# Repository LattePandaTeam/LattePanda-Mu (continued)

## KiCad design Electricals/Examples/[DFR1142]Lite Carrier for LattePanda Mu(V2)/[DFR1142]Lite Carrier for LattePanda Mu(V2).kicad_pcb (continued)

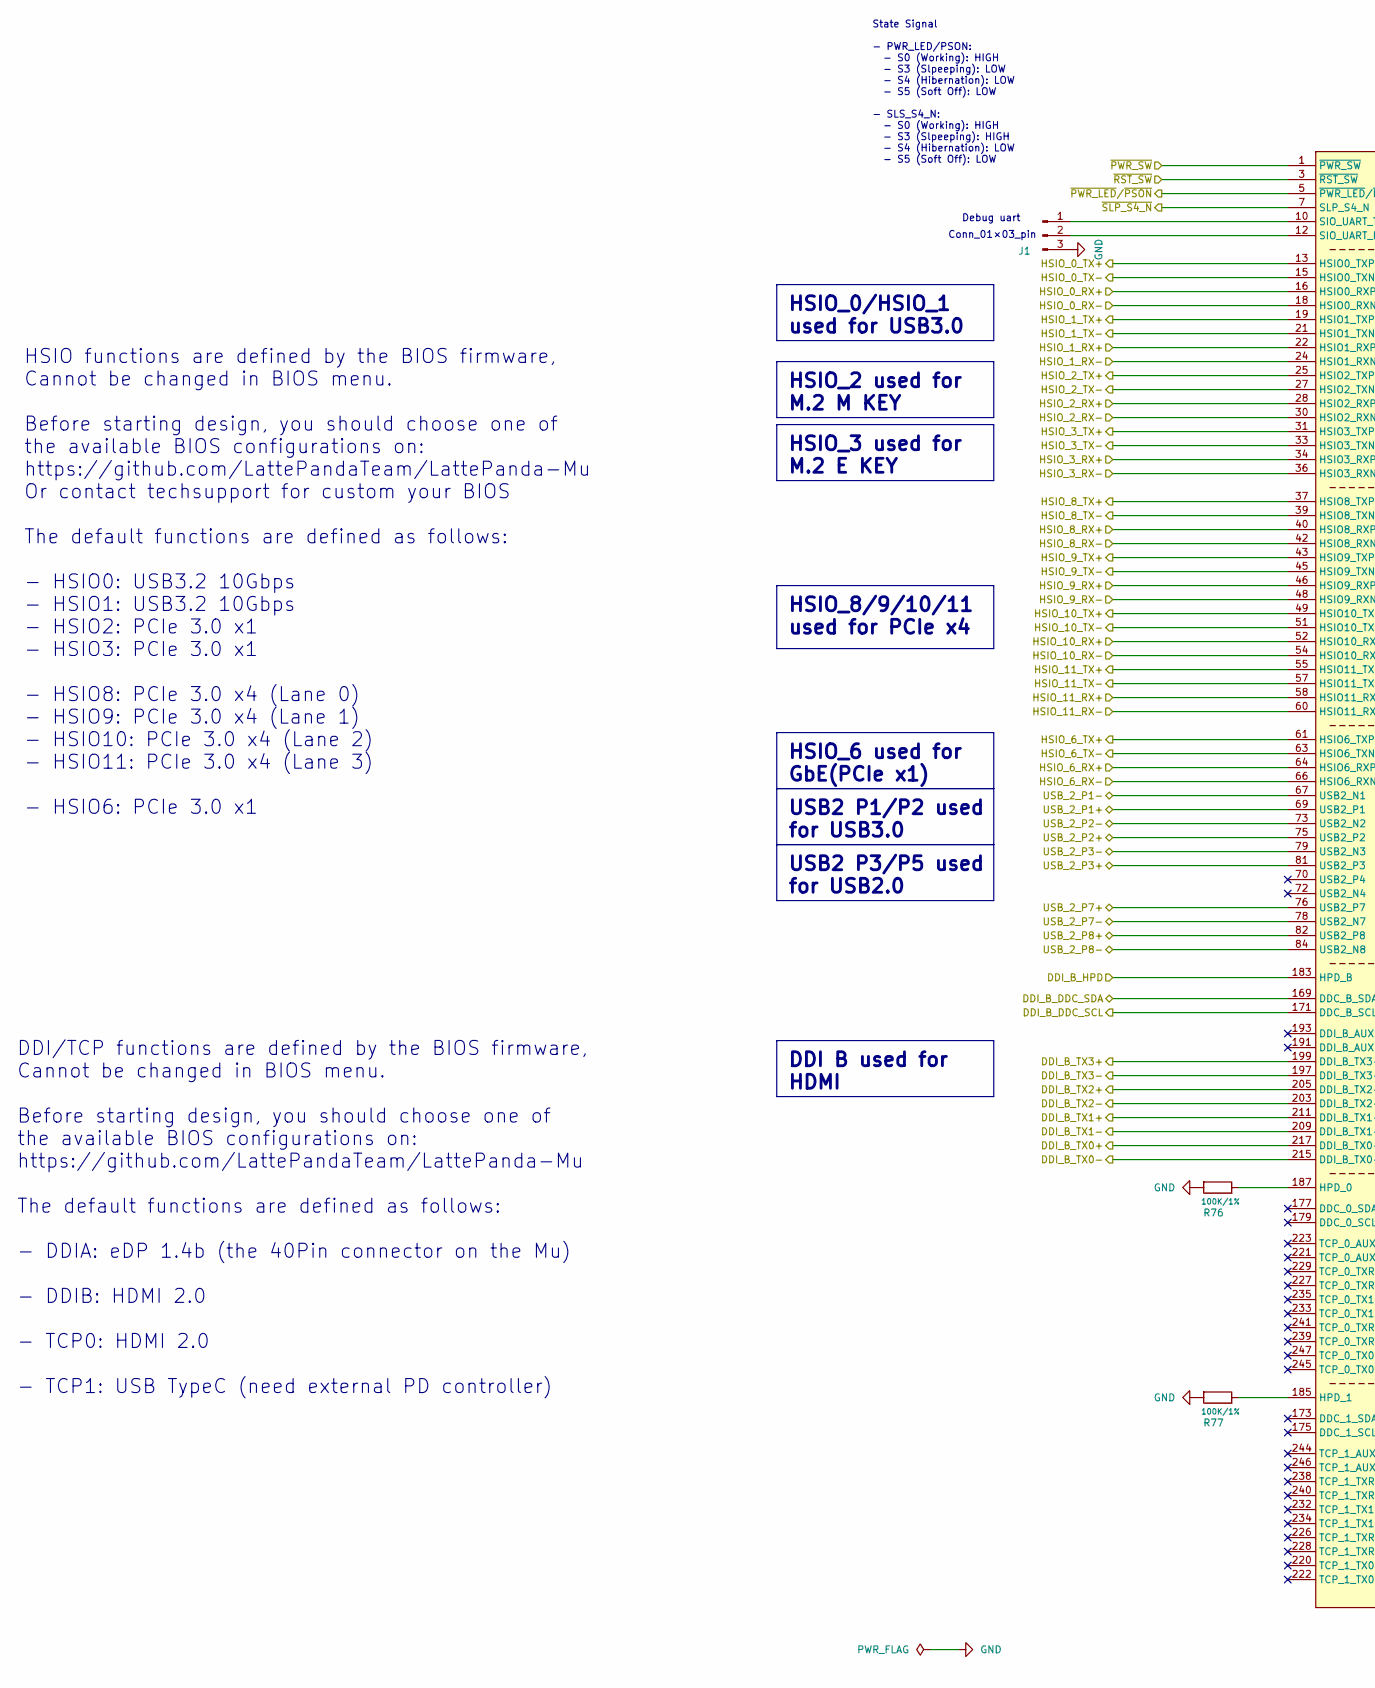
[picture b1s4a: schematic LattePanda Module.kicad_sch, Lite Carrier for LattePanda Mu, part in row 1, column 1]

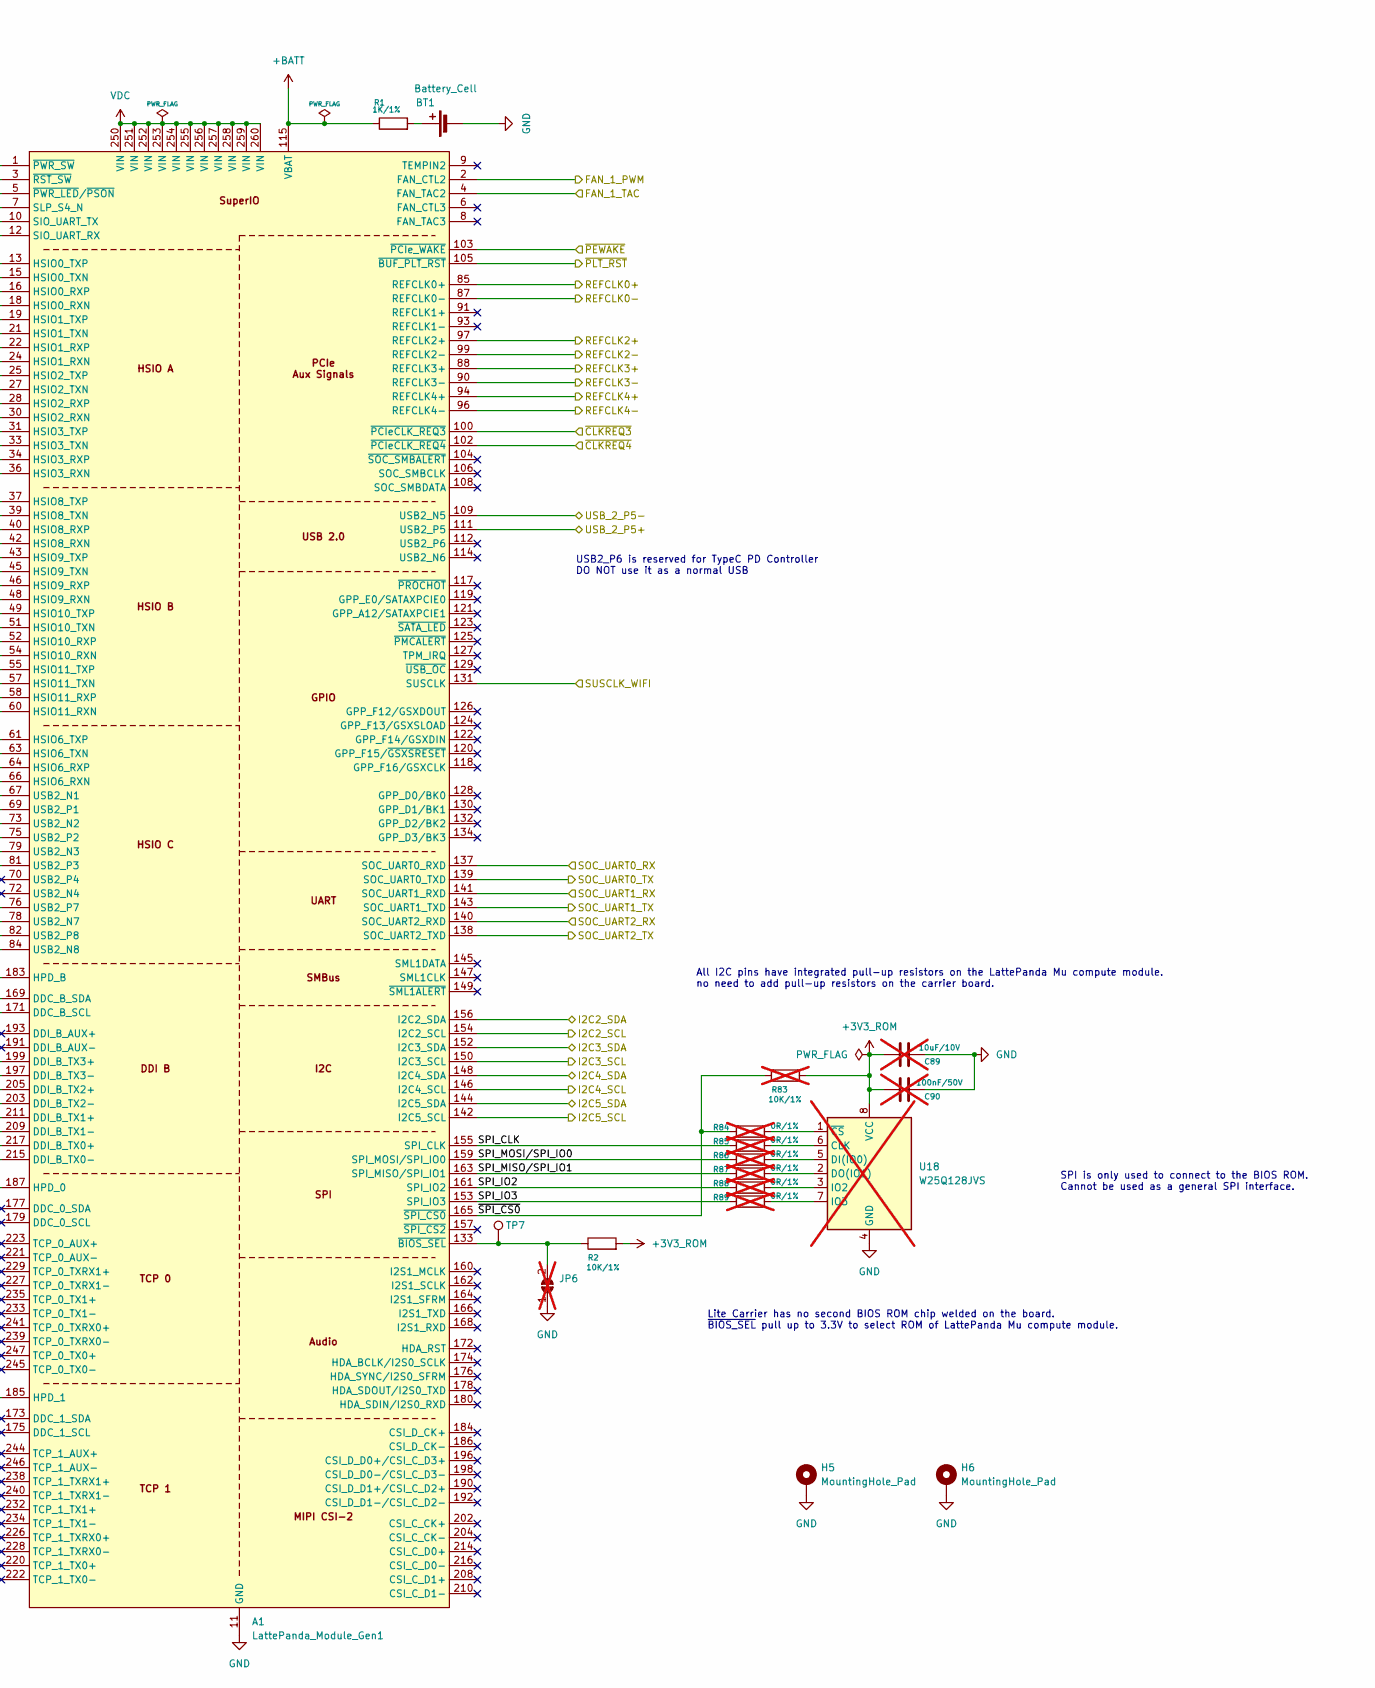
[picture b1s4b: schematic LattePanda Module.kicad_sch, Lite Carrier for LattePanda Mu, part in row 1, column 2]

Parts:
A1: LattePanda_Module_Gen1; DDR4_SODIMM_260P_8.0H_STD
BT1: Battery_Cell; Battery_Holder_CR1220_S8411-45R
C89: 10uF/10V; C_0402; not fitted
C90: 100nF/50V; C_0402; not fitted
H5, H6: MountingHole_Pad; MountingHole_3mm_M2_Pad_TopOnly
J1: Conn_01x03_Pin; PinHeader_1x03_P2.54mm_Vertical
JP6: SolderJumper_2_Open; SolderJumper-2_P1.3mm_Open_TrianglePad1.0x1.5mm; not fitted
R1: 1K/1%; R_0402
R2: 10K/1%; R_0402
R76, R77: 100K/1%; R_0402
R83: 10K/1%; R_0402; not fitted
R84, R85, R86, R87, R88, R89: 0R/1%; R_0402; not fitted
TP7: TestPoint; TestPoint_Pad_D1.5mm
U18: W25Q128JVS; SOIC-8_5.23x5.23mm_P1.27mm; not fitted

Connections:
+3V3_ROM: C89.2, C90.2, R2.2, R83.2, U18.8 (VCC); also elsewhere on the board
+BATT: A1.115 (VBAT), R1.1
/Fan_Temp/FAN_1_PWM: A1.2 (FAN_CTL2); also elsewhere on the board
/Fan_Temp/FAN_1_TAC: A1.4 (FAN_TAC2); also elsewhere on the board
/GPIO/I2C2_SCL: A1.154 (I2C2_SCL); also elsewhere on the board
/GPIO/I2C2_SDA: A1.156 (I2C2_SDA); also elsewhere on the board
/GPIO/I2C3_SCL: A1.150 (I2C3_SCL); also elsewhere on the board
/GPIO/I2C3_SDA: A1.152 (I2C3_SDA); also elsewhere on the board
/GPIO/I2C4_SCL: A1.146 (I2C4_SCL); also elsewhere on the board
/GPIO/I2C4_SDA: A1.148 (I2C4_SDA); also elsewhere on the board
/GPIO/I2C5_SCL: A1.142 (I2C5_SCL); also elsewhere on the board
/GPIO/I2C5_SDA: A1.144 (I2C5_SDA); also elsewhere on the board
/GPIO/SOC_UART0_RX: A1.137 (SOC_UART0_RXD); also elsewhere on the board
/GPIO/SOC_UART0_TX: A1.139 (SOC_UART0_TXD); also elsewhere on the board
/GPIO/SOC_UART1_RX: A1.141 (SOC_UART1_RXD); also elsewhere on the board
/GPIO/SOC_UART1_TX: A1.143 (SOC_UART1_TXD); also elsewhere on the board
/GPIO/SOC_UART2_RX: A1.140 (SOC_UART2_RXD); also elsewhere on the board
/GPIO/SOC_UART2_TX: A1.138 (SOC_UART2_TXD); also elsewhere on the board
/Gigabit Ethernet/GbE_PCIe_CLK+: A1.94 (REFCLK4+); also elsewhere on the board
/Gigabit Ethernet/GbE_PCIe_CLK-: A1.96 (REFCLK4-); also elsewhere on the board
/Gigabit Ethernet/GbE_PCIe_RX+: A1.64 (HSIO6_RXP); also elsewhere on the board
/Gigabit Ethernet/GbE_PCIe_RX-: A1.66 (HSIO6_RXN); also elsewhere on the board
/Gigabit Ethernet/GbE_PCIe_TX+: A1.61 (HSIO6_TXP); also elsewhere on the board
/Gigabit Ethernet/GbE_PCIe_TX-: A1.63 (HSIO6_TXN); also elsewhere on the board
/Gigabit Ethernet/~CLKREQ4: A1.102 (~PCIeCLK_REQ4); also elsewhere on the board
/HDMI/DDI_B_DDC_SCL: A1.171 (DDC_B_SCL); also elsewhere on the board
/HDMI/DDI_B_DDC_SDA: A1.169 (DDC_B_SDA); also elsewhere on the board
/HDMI/DDI_B_HPD: A1.183 (HPD_B); also elsewhere on the board
/HDMI/DDI_B_TX0+: A1.217 (DDI_B_TX0+); also elsewhere on the board
/HDMI/DDI_B_TX0-: A1.215 (DDI_B_TX0-); also elsewhere on the board
/HDMI/DDI_B_TX1+: A1.211 (DDI_B_TX1+); also elsewhere on the board
/HDMI/DDI_B_TX1-: A1.209 (DDI_B_TX1-); also elsewhere on the board
/HDMI/DDI_B_TX2+: A1.205 (DDI_B_TX2+); also elsewhere on the board
/HDMI/DDI_B_TX2-: A1.203 (DDI_B_TX2-); also elsewhere on the board
/HDMI/DDI_B_TX3+: A1.199 (DDI_B_TX3+); also elsewhere on the board
/HDMI/DDI_B_TX3-: A1.197 (DDI_B_TX3-); also elsewhere on the board
/LattePanda Module/HSIO_0_TX+: A1.13 (HSIO0_TXP); also elsewhere on the board
/LattePanda Module/HSIO_0_TX-: A1.15 (HSIO0_TXN); also elsewhere on the board
/LattePanda Module/HSIO_1_TX+: A1.19 (HSIO1_TXP); also elsewhere on the board
/LattePanda Module/HSIO_1_TX-: A1.21 (HSIO1_TXN); also elsewhere on the board
/LattePanda Module/HSIO_2_RX+: A1.28 (HSIO2_RXP); also elsewhere on the board
/LattePanda Module/HSIO_2_RX-: A1.30 (HSIO2_RXN); also elsewhere on the board
/LattePanda Module/HSIO_2_TX+: A1.25 (HSIO2_TXP); also elsewhere on the board
/LattePanda Module/HSIO_2_TX-: A1.27 (HSIO2_TXN); also elsewhere on the board
/LattePanda Module/HSIO_3_RX+: A1.34 (HSIO3_RXP); also elsewhere on the board
/LattePanda Module/HSIO_3_RX-: A1.36 (HSIO3_RXN); also elsewhere on the board
/LattePanda Module/HSIO_3_TX+: A1.31 (HSIO3_TXP); also elsewhere on the board
/LattePanda Module/HSIO_3_TX-: A1.33 (HSIO3_TXN); also elsewhere on the board
/LattePanda Module/HSIO_8_RX+: A1.40 (HSIO8_RXP); also elsewhere on the board
/LattePanda Module/HSIO_8_RX-: A1.42 (HSIO8_RXN); also elsewhere on the board
/LattePanda Module/HSIO_8_TX+: A1.37 (HSIO8_TXP); also elsewhere on the board
/LattePanda Module/HSIO_8_TX-: A1.39 (HSIO8_TXN); also elsewhere on the board
/LattePanda Module/HSIO_9_RX+: A1.46 (HSIO9_RXP); also elsewhere on the board
/LattePanda Module/HSIO_9_RX-: A1.48 (HSIO9_RXN); also elsewhere on the board
/LattePanda Module/HSIO_9_TX+: A1.43 (HSIO9_TXP); also elsewhere on the board
/LattePanda Module/HSIO_9_TX-: A1.45 (HSIO9_TXN); also elsewhere on the board
/LattePanda Module/HSIO_10_RX+: A1.52 (HSIO10_RXP); also elsewhere on the board
/LattePanda Module/HSIO_10_RX-: A1.54 (HSIO10_RXN); also elsewhere on the board
/LattePanda Module/HSIO_10_TX+: A1.49 (HSIO10_TXP); also elsewhere on the board
/LattePanda Module/HSIO_10_TX-: A1.51 (HSIO10_TXN); also elsewhere on the board
/LattePanda Module/HSIO_11_RX+: A1.58 (HSIO11_RXP); also elsewhere on the board
/LattePanda Module/HSIO_11_RX-: A1.60 (HSIO11_RXN); also elsewhere on the board
/LattePanda Module/HSIO_11_TX+: A1.55 (HSIO11_TXP); also elsewhere on the board
/LattePanda Module/HSIO_11_TX-: A1.57 (HSIO11_TXN); also elsewhere on the board
/LattePanda Module/REFCLK0+: A1.85 (REFCLK0+); also elsewhere on the board
/LattePanda Module/REFCLK0-: A1.87 (REFCLK0-); also elsewhere on the board
/LattePanda Module/REFCLK2+: A1.97 (REFCLK2+); also elsewhere on the board
/LattePanda Module/REFCLK2-: A1.99 (REFCLK2-); also elsewhere on the board
/LattePanda Module/REFCLK3+: A1.88 (REFCLK3+); also elsewhere on the board
/LattePanda Module/REFCLK3-: A1.90 (REFCLK3-); also elsewhere on the board
/LattePanda Module/SPI_CLK: A1.155 (SPI_CLK), R85.2
/LattePanda Module/SPI_IO2: A1.161 (SPI_IO2), R88.2
/LattePanda Module/SPI_IO3: A1.153 (SPI_IO3), R89.2
/LattePanda Module/SPI_MISO/SPI_IO1: A1.163 (SPI_MISO/SPI_IO1), R87.2
/LattePanda Module/SPI_MOSI/SPI_IO0: A1.159 (SPI_MOSI/SPI_IO0), R86.2
/LattePanda Module/SUSCLK_WIFI: A1.131 (SUSCLK); also elsewhere on the board
/LattePanda Module/USB_2_P4+: A1.70 (USB2_P4)
/LattePanda Module/USB_2_P4-: A1.72 (USB2_N4)
/LattePanda Module/USB_2_P7+: A1.76 (USB2_P7); also elsewhere on the board
/LattePanda Module/USB_2_P7-: A1.78 (USB2_N7); also elsewhere on the board
/LattePanda Module/~CLKREQ3: A1.100 (~PCIeCLK_REQ3); also elsewhere on the board
/LattePanda Module/~PWR_SW: A1.1 (~PWR_SW); also elsewhere on the board
/LattePanda Module/~RST_SW: A1.3 (~RST_SW); also elsewhere on the board
/LattePanda Module/~SPI_CS0: A1.165 (~SPI_CS0), R83.1, R84.2
/PSU/UPS_USB_DN: A1.84 (USB2_N8); also elsewhere on the board
/PSU/UPS_USB_DP: A1.82 (USB2_P8); also elsewhere on the board
/PSU/~SLP_S4_N: A1.7 (SLP_S4_N); also elsewhere on the board
/USB2.0&USB3.0/CON_USB1_D_N: A1.109 (USB2_N5); also elsewhere on the board
/USB2.0&USB3.0/CON_USB1_D_P: A1.111 (USB2_P5); also elsewhere on the board
/USB2.0&USB3.0/CON_USB2_D_N: A1.79 (USB2_N3); also elsewhere on the board
/USB2.0&USB3.0/CON_USB2_D_P: A1.81 (USB2_P3); also elsewhere on the board
/USB2.0&USB3.0/CON_USB3_D_N: A1.73 (USB2_N2); also elsewhere on the board
/USB2.0&USB3.0/CON_USB3_D_P: A1.75 (USB2_P2); also elsewhere on the board
/USB2.0&USB3.0/CON_USB3_SSRX_N: A1.18 (HSIO0_RXN); also elsewhere on the board
/USB2.0&USB3.0/CON_USB3_SSRX_P: A1.16 (HSIO0_RXP); also elsewhere on the board
/USB2.0&USB3.0/CON_USB4_D_N: A1.67 (USB2_N1); also elsewhere on the board
/USB2.0&USB3.0/CON_USB4_D_P: A1.69 (USB2_P1); also elsewhere on the board
/USB2.0&USB3.0/CON_USB4_SSRX_N: A1.24 (HSIO1_RXN); also elsewhere on the board
/USB2.0&USB3.0/CON_USB4_SSRX_P: A1.22 (HSIO1_RXP); also elsewhere on the board
/~PLT_RST: A1.105 (~BUF_PLT_RST); also elsewhere on the board
/~PWR_LED/~PSON: A1.5 (~PWR_LED/~PSON); also elsewhere on the board
/~WAKE: A1.103 (~PCIe_WAKE); also elsewhere on the board
GND: A1.11 (GND), A1.14 (GND), A1.17 (GND), A1.20 (GND), A1.23 (GND), A1.26 (GND), A1.29 (GND), A1.32 (GND), A1.35 (GND), A1.38 (GND), A1.41 (GND), A1.44 (GND), A1.47 (GND), A1.50 (GND), A1.53 (GND), A1.56 (GND), A1.59 (GND), A1.62 (GND), A1.65 (GND), A1.68 (GND), A1.71 (GND), A1.74 (GND), A1.77 (GND), A1.80 (GND), A1.83 (GND), A1.86 (GND), A1.89 (GND), A1.92 (GND), A1.95 (GND), A1.98 (GND), A1.101 (GND), A1.107 (GND), A1.110 (GND), A1.113 (GND), A1.116 (GND), A1.135 (GND), A1.136 (GND), A1.151 (GND), A1.158 (GND), A1.167 (GND), A1.170 (GND), A1.181 (GND), A1.182 (GND), A1.188 (GND), A1.189 (GND), A1.194 (GND), A1.195 (GND), A1.200 (GND), A1.201 (GND), A1.206 (GND), A1.207 (GND), A1.212 (GND), A1.213 (GND), A1.218 (GND), A1.219 (GND), A1.224 (GND), A1.225 (GND), A1.230 (GND), A1.231 (GND), A1.236 (GND), A1.237 (GND), A1.242 (GND), A1.243 (GND), A1.248 (GND), A1.249 (GND), A1.MP1, A1.MP2, BT1.2 (-), C89.1, C90.1, H5.1, H6.1, J1.3, JP6.1 (A), R76.2, R77.2, U18.4 (GND); also elsewhere on the board
unnamed: A1.187 (HPD_0), R76.1
unnamed: A1.185 (HPD_1), R77.1
unnamed: A1.12 (SIO_UART_RX), J1.2
unnamed: A1.10 (SIO_UART_TX), J1.1
unnamed: A1.133 (~BIOS_SEL), JP6.2 (B), R2.1, TP7.1
unnamed: BT1.1 (+), R1.2
unnamed: R85.1, U18.6 (CLK)
unnamed: R86.1, U18.5 (DI(IO0))
unnamed: R87.1, U18.2 (DO(IO1))
unnamed: R88.1, U18.3 (IO2)
unnamed: R89.1, U18.7 (IO3)
unnamed: R84.1, U18.1 (~CS)
VDC: A1.250 (VIN), A1.251 (VIN), A1.252 (VIN), A1.253 (VIN), A1.254 (VIN), A1.255 (VIN), A1.256 (VIN), A1.257 (VIN), A1.258 (VIN), A1.259 (VIN), A1.260 (VIN); also elsewhere on the board

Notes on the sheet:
State Signal - PWR_LED/PSON: - S0 (Working): HIGH - S3 (Slpeeping): LOW - S4 (Hibernation): LOW - S5 (Soft Off): LOW - SLS_S4_N: - S0 (Working): HIGH - S3 (Slpeeping): HIGH - S4 (Hibernation): LOW - S5 (Soft Off): LOW
DDI/TCP functions are defined by the BIOS firmware, Cannot be changed in BIOS menu. Before starting design, you should choose one of the available BIOS configurations on: https://github.com/LattePandaTeam/LattePanda-Mu The default functions are defined as follows: - DDIA: eDP 1.4b (the 40Pin connec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
Lite Carrier has no second BIOS ROM chip welded on the board. ~{BIOS_SEL} pull up to 3.3V to select ROM of LattePanda Mu compute module.
USB2_P6 is reserved for TypeC PD Controller DO NOT use it as a normal USB
Debug uart
Conn_01×03_pin
SPI is only used to connect to the BIOS ROM. Cannot be used as a general SPI interface.
HSIO functions are defined by the BIOS firmware, Cannot be changed in BIOS menu. Before starting design, you should choose one of the available BIOS configurations on: https://github.com/LattePandaTeam/LattePanda-Mu Or contact techsupport for custom your BIOS The default functions are defined as fo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
All I2C pins have integrated pull-up resistors on the LattePanda Mu compute module. no need to add pull-up resistors on the carrier board.
HSIO_0/HSIO_1 used for USB3.0
HSIO_2 used for M.2 M KEY
HSIO_6 used for GbE(PCIe x1)
USB2 P3/P5 used for USB2.0
DDI B used for HDMI
HSIO_3 used for M.2 E KEY
HSIO_8/9/10/11 used for PCIe x4
USB2 P1/P2 used for USB3.0

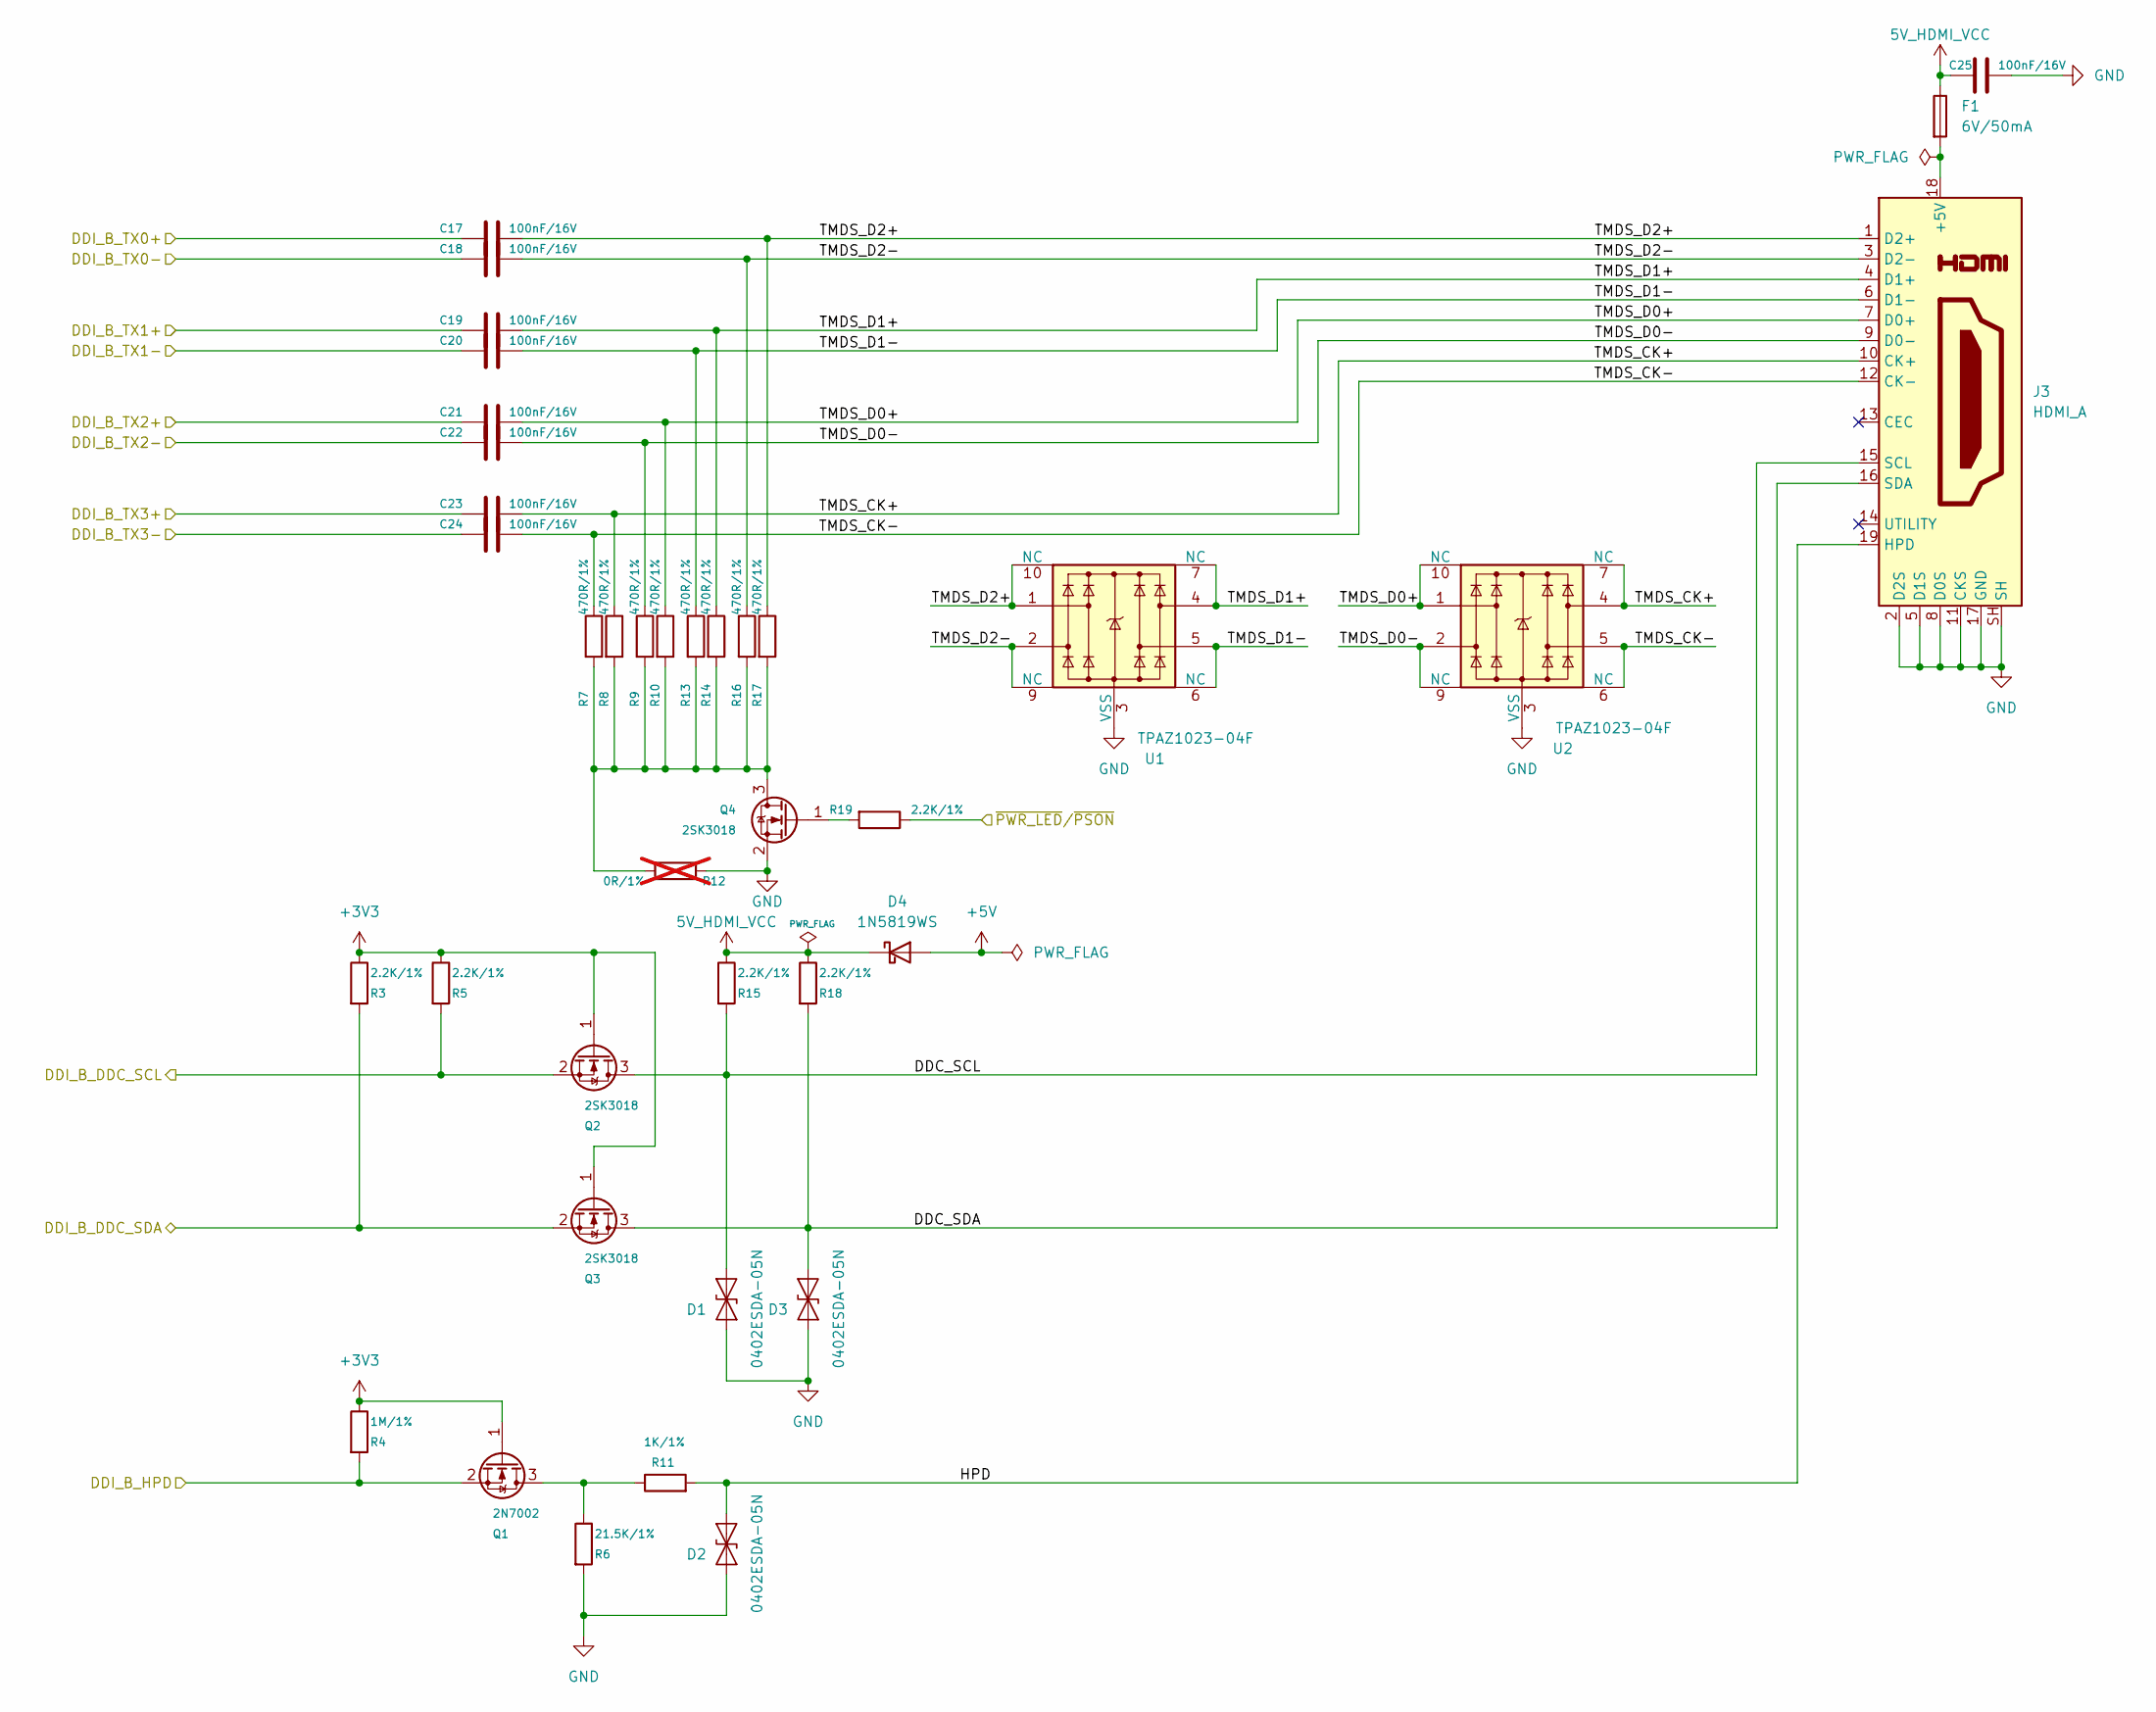
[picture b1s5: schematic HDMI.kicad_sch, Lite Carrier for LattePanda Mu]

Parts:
C17, C18, C19, C20, C21, C22, C23, C24, C25: 100nF/16V; C_0402_1005Metric
D1, D2, D3: 0402ESDA-05N; D_0402_1005Metric
D4: 1N5819WS; D_SOD-323
F1: 6V/50mA; R_0603_1608Metric
J3: HDMI_A; HDMI_A_Molex_208658-1001_Horizontal
Q1: 2N7002; SOT-23
Q2, Q3, Q4: 2SK3018; SOT-23
R3, R5, R15, R18, R19: 2.2K/1%; R_0402
R4: 1M/1%; R_0402
R6: 21.5K/1%; R_0402
R7, R8, R9, R10, R13, R14, R16, R17: 470R/1%; R_0402
R11: 1K/1%; R_0402
R12: 0R/1%; R_0402_1005Metric; not fitted
U1, U2: TPAZ1023-04F; Diodes_UDFN-10_1.0x2.5mm_P0.5mm

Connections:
5V_HDMI_VCC: C25.1, D4.1 (K), F1.1, R15.1, R18.1
+3V3: Q1.1 (G), Q2.1 (G), Q3.1 (G), R3.1, R4.1, R5.1; also elsewhere on the board
+5V: D4.2 (A); also elsewhere on the board
/HDMI/DDC_SCL: D1.2 (A2), J3.15 (SCL), Q2.3 (D), R15.2
/HDMI/DDC_SDA: D3.2 (A2), J3.16 (SDA), Q3.3 (D), R18.2
/HDMI/DDI_B_DDC_SCL: Q2.2 (S), R5.2; also elsewhere on the board
/HDMI/DDI_B_DDC_SDA: Q3.2 (S), R3.2; also elsewhere on the board
/HDMI/DDI_B_HPD: Q1.2 (S), R4.2; also elsewhere on the board
/HDMI/DDI_B_TX0+: C17.1; also elsewhere on the board
/HDMI/DDI_B_TX0-: C18.1; also elsewhere on the board
/HDMI/DDI_B_TX1+: C19.1; also elsewhere on the board
/HDMI/DDI_B_TX1-: C20.1; also elsewhere on the board
/HDMI/DDI_B_TX2+: C21.1; also elsewhere on the board
/HDMI/DDI_B_TX2-: C22.1; also elsewhere on the board
/HDMI/DDI_B_TX3+: C23.1; also elsewhere on the board
/HDMI/DDI_B_TX3-: C24.1; also elsewhere on the board
/HDMI/HPD: D2.2 (A2), J3.19 (HPD), R11.2
/HDMI/TMDS_CK+: C23.2, J3.10 (CK+), R8.1, U2.4, U2.7 (NC)
/HDMI/TMDS_CK-: C24.2, J3.12 (CK-), R7.1, U2.5, U2.6 (NC)
/HDMI/TMDS_D0+: C21.2, J3.7 (D0+), R10.1, U2.1, U2.10 (NC)
/HDMI/TMDS_D0-: C22.2, J3.9 (D0-), R9.1, U2.2, U2.9 (NC)
/HDMI/TMDS_D1+: C19.2, J3.4 (D1+), R14.1, U1.4, U1.7 (NC)
/HDMI/TMDS_D1-: C20.2, J3.6 (D1-), R13.1, U1.5, U1.6 (NC)
/HDMI/TMDS_D2+: C17.2, J3.1 (D2+), R17.1, U1.1, U1.10 (NC)
/HDMI/TMDS_D2-: C18.2, J3.3 (D2-), R16.1, U1.2, U1.9 (NC)
/~PWR_LED/~PSON: R19.1; also elsewhere on the board
GND: C25.2, D1.1 (A1), D2.1 (A1), D3.1 (A1), J3.2 (D2S), J3.5 (D1S), J3.8 (D0S), J3.11 (CKS), J3.17 (GND), J3.SH, Q4.2 (S), R6.2, R12.2, U1.3 (VSS), U1.8 (VSS), U2.3 (VSS), U2.8 (VSS); also elsewhere on the board
unnamed: F1.2, J3.18 (+5V)
unnamed: Q1.3 (D), R6.1, R11.1
unnamed: Q4.3 (D), R7.2, R8.2, R9.2, R10.2, R12.1, R13.2, R14.2, R16.2, R17.2
unnamed: Q4.1 (G), R19.2
